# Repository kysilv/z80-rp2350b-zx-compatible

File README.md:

# z80-rp2350b-zx-compatible
This is a retrocomputer compatible with ZX Spectrum and based on real Z80 + discrete RAM/ROM + rp2350b to cover ULA functionality programmatically.

## Specification:

**CPU**: Z84C00AB6 Z80A CPU DIP-40

**ROM**: W27c512-45z DIP-28

**RAM**: 2xHM62256ALP-10 DIP-28

**ULA**: WeAct RP2350B Core board

**Video**: VGA (DE-15) and DVI over HDMI connector, 720x576p emulating Spectrum PAL resolution.

**Audio**: Speaker on board

**Cassette interface**: Jack 3.5mm for smartphone headset jack

**Keyboard**: Handmade

**Joystick**: 
  1. Retro DA-15 GamePort joystick interface connected to expansion connector, emulating Kempston port 1F.
  2. Sinclair Joystick 1 in parallel to keyboard 6-0 (connector not soldered yet).

## Folders:

**firmware**: Source code for rp2350b covering ULA functionality (C + PIO ASM)

**hardware**: Pictures of schematic and pcbs, KiCAD projects of the computer and Joystick interface. There are pictures of the first version with a lot of fixes. 

**photos**: Photos of the device in process of tuning and some "screenshots".

Press: https://hackaday.com/2026/07/13/its-a-spectrum-with-an-rp2350-ula/

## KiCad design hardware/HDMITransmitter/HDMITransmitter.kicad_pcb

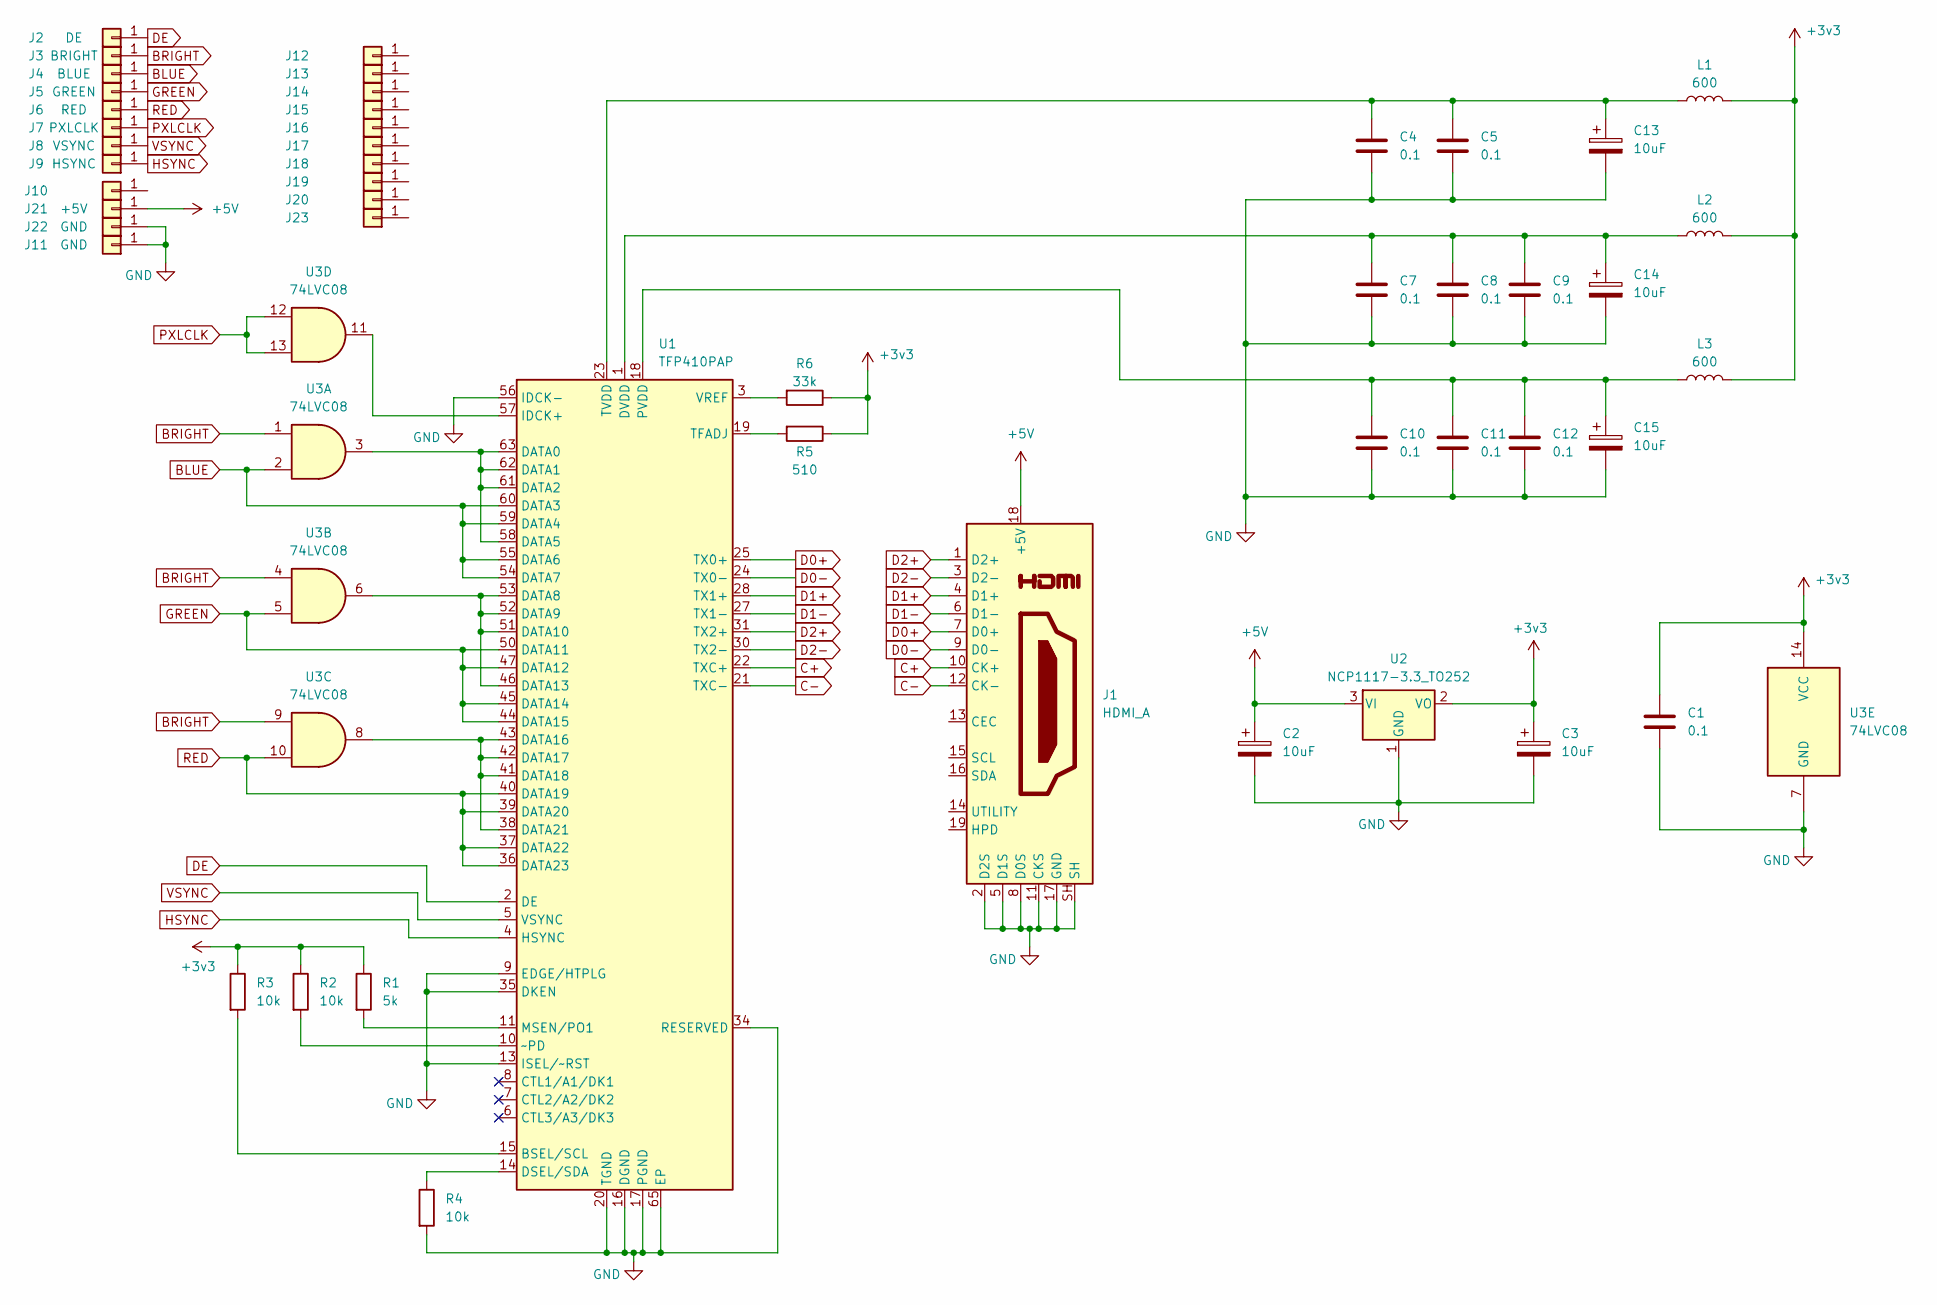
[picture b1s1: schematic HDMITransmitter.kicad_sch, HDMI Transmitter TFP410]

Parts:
C1, C4, C5, C7, C8, C9, C10, C11, C12: 0.1; C_0603_1608Metric_Pad1.08x0.95mm_HandSolder
C2, C3, C13, C14, C15: 10uF; CP_EIA-3216-18_Kemet-A_HandSolder
J1: HDMI_A; HDMI_A_Molex_208658-1001_Horizontal
J2: DE; Pin_D1.0mm_L10.0mm
J3: BRIGHT; Pin_D1.0mm_L10.0mm
J4: BLUE; Pin_D1.0mm_L10.0mm
J5: GREEN; Pin_D1.0mm_L10.0mm
J6: RED; Pin_D1.0mm_L10.0mm
J7: PXLCLK; Pin_D1.0mm_L10.0mm
J8: VSYNC; Pin_D1.0mm_L10.0mm
J9: HSYNC; Pin_D1.0mm_L10.0mm
J10, J12, J13, J14, J15, J16, J17, J18, J19, J20, J23: Pin_D1.0mm_L10.0mm
J11, J22: GND; Pin_D1.0mm_L10.0mm
J21: +5V; Pin_D1.0mm_L10.0mm
L1, L2, L3: 600; L_0603_1608Metric_Pad1.05x0.95mm_HandSolder
R1: 5k; R_0603_1608Metric_Pad0.98x0.95mm_HandSolder
R2, R3, R4: 10k; R_0603_1608Metric_Pad0.98x0.95mm_HandSolder
R5: 510; R_0603_1608Metric_Pad0.98x0.95mm_HandSolder
R6: 33k; R_0603_1608Metric_Pad0.98x0.95mm_HandSolder
U1: TFP410PAP; Texas_TQFP-64-1EP_10x10mm_P0.5mm_EP8x8mm_Mask5x5mm_ThermalV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
U2: NCP1117-3.3_TO252; TO-252-2
U3: 74LVC08; SOIC-14_3.9x8.7mm_P1.27mm

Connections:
+3v3: C1.1, C3.1, L1.2, L2.2, L3.2, R1.1, R2.1, R3.1, R5.1, R6.1, U2.2 (VO), U3.14 (VCC)
+5V: C2.1, J1.18 (+5V), J21.1, U2.3 (VI)
BLUE: J4.1, U1.54 (DATA7), U1.55 (DATA6), U1.59 (DATA4), U1.60 (DATA3), U3.2
BRIGHT: J3.1, U3.1, U3.4, U3.9
C+: J1.10 (CK+), U1.22 (TXC+)
C-: J1.12 (CK-), U1.21 (TXC-)
D0+: J1.7 (D0+), U1.25 (TX0+)
D0-: J1.9 (D0-), U1.24 (TX0-)
D1+: J1.4 (D1+), U1.28 (TX1+)
D1-: J1.6 (D1-), U1.27 (TX1-)
D2+: J1.1 (D2+), U1.31 (TX2+)
D2-: J1.3 (D2-), U1.30 (TX2-)
DE: J2.1, U1.2 (DE)
GND: C1.2, C2.2, C3.2, C4.2, C5.2, C7.2, C8.2, C9.2, C10.2, C11.2, C12.2, C13.2, C14.2, C15.2, J1.2 (D2S), J1.5 (D1S), J1.8 (D0S), J1.11 (CKS), J1.17 (GND), J1.SH, J11.1, J22.1, R4.2, U1.9 (EDGE/HTPLG), U1.13 (ISEL/~RST), U1.16 (DGND), U1.17 (PGND), U1.20 (TGND), U1.26 (TGND), U1.32 (TGND), U1.34 (RESERVED), U1.35 (DKEN), U1.48 (DGND), U1.56 (IDCK-), U1.64 (DGND), U1.65 (EP), U2.1 (GND), U3.7 (GND)
GREEN: J5.1, U1.44 (DATA15), U1.45 (DATA14), U1.47 (DATA12), U1.50 (DATA11), U3.5
HSYNC: J9.1, U1.4 (HSYNC)
unnamed: C4.1, C5.1, C13.1, L1.1, U1.23 (TVDD), U1.29 (TVDD)
unnamed: C7.1, C8.1, C9.1, C14.1, L2.1, U1.1 (DVDD), U1.12 (DVDD), U1.33 (DVDD)
unnamed: R3.2, U1.15 (BSEL/SCL)
unnamed: U1.58 (DATA5), U1.61 (DATA2), U1.62 (DATA1), U1.63 (DATA0), U3.3
unnamed: U1.46 (DATA13), U1.51 (DATA10), U1.52 (DATA9), U1.53 (DATA8), U3.6
unnamed: U1.38 (DATA21), U1.41 (DATA18), U1.42 (DATA17), U1.43 (DATA16), U3.8
unnamed: R4.1, U1.14 (DSEL/SDA)
unnamed: U1.57 (IDCK+), U3.11
unnamed: R1.2, U1.11 (MSEN/PO1)
unnamed: C10.1, C11.1, C12.1, C15.1, L3.1, U1.18 (PVDD)
unnamed: R5.2, U1.19 (TFADJ)
unnamed: R6.2, U1.3 (VREF)
unnamed: R2.2, U1.10 (~PD)
PXLCLK: J7.1, U3.12, U3.13
RED: J6.1, U1.36 (DATA23), U1.37 (DATA22), U1.39 (DATA20), U1.40 (DATA19), U3.10
VSYNC: J8.1, U1.5 (VSYNC)

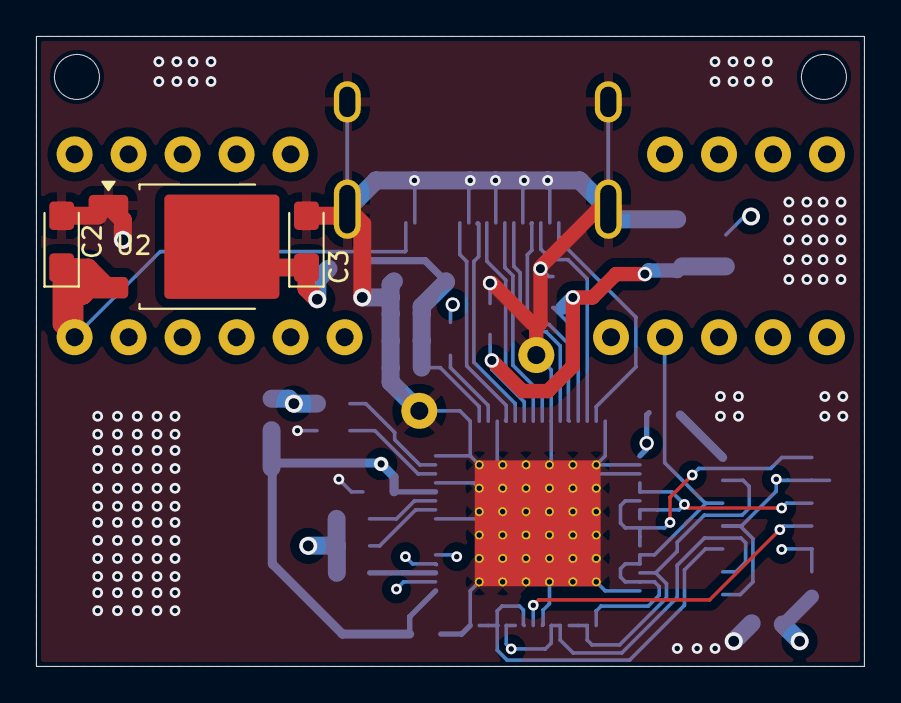
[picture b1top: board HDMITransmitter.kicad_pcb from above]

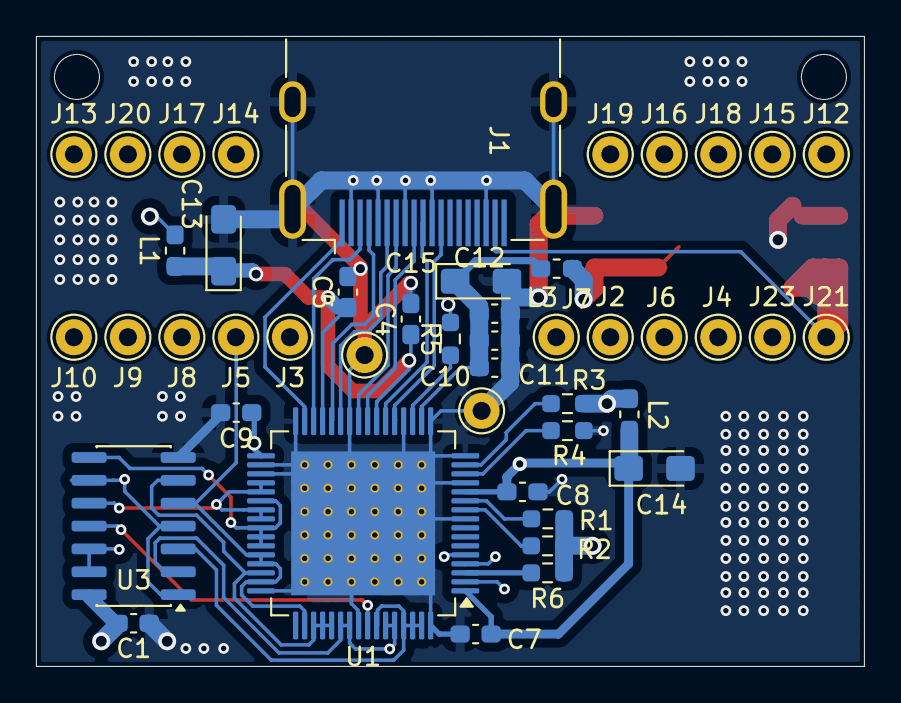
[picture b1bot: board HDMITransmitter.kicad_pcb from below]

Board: 4 copper layers, 46.0 x 35.0 mm, 49 parts (46 on the bottom side), 32 nets.

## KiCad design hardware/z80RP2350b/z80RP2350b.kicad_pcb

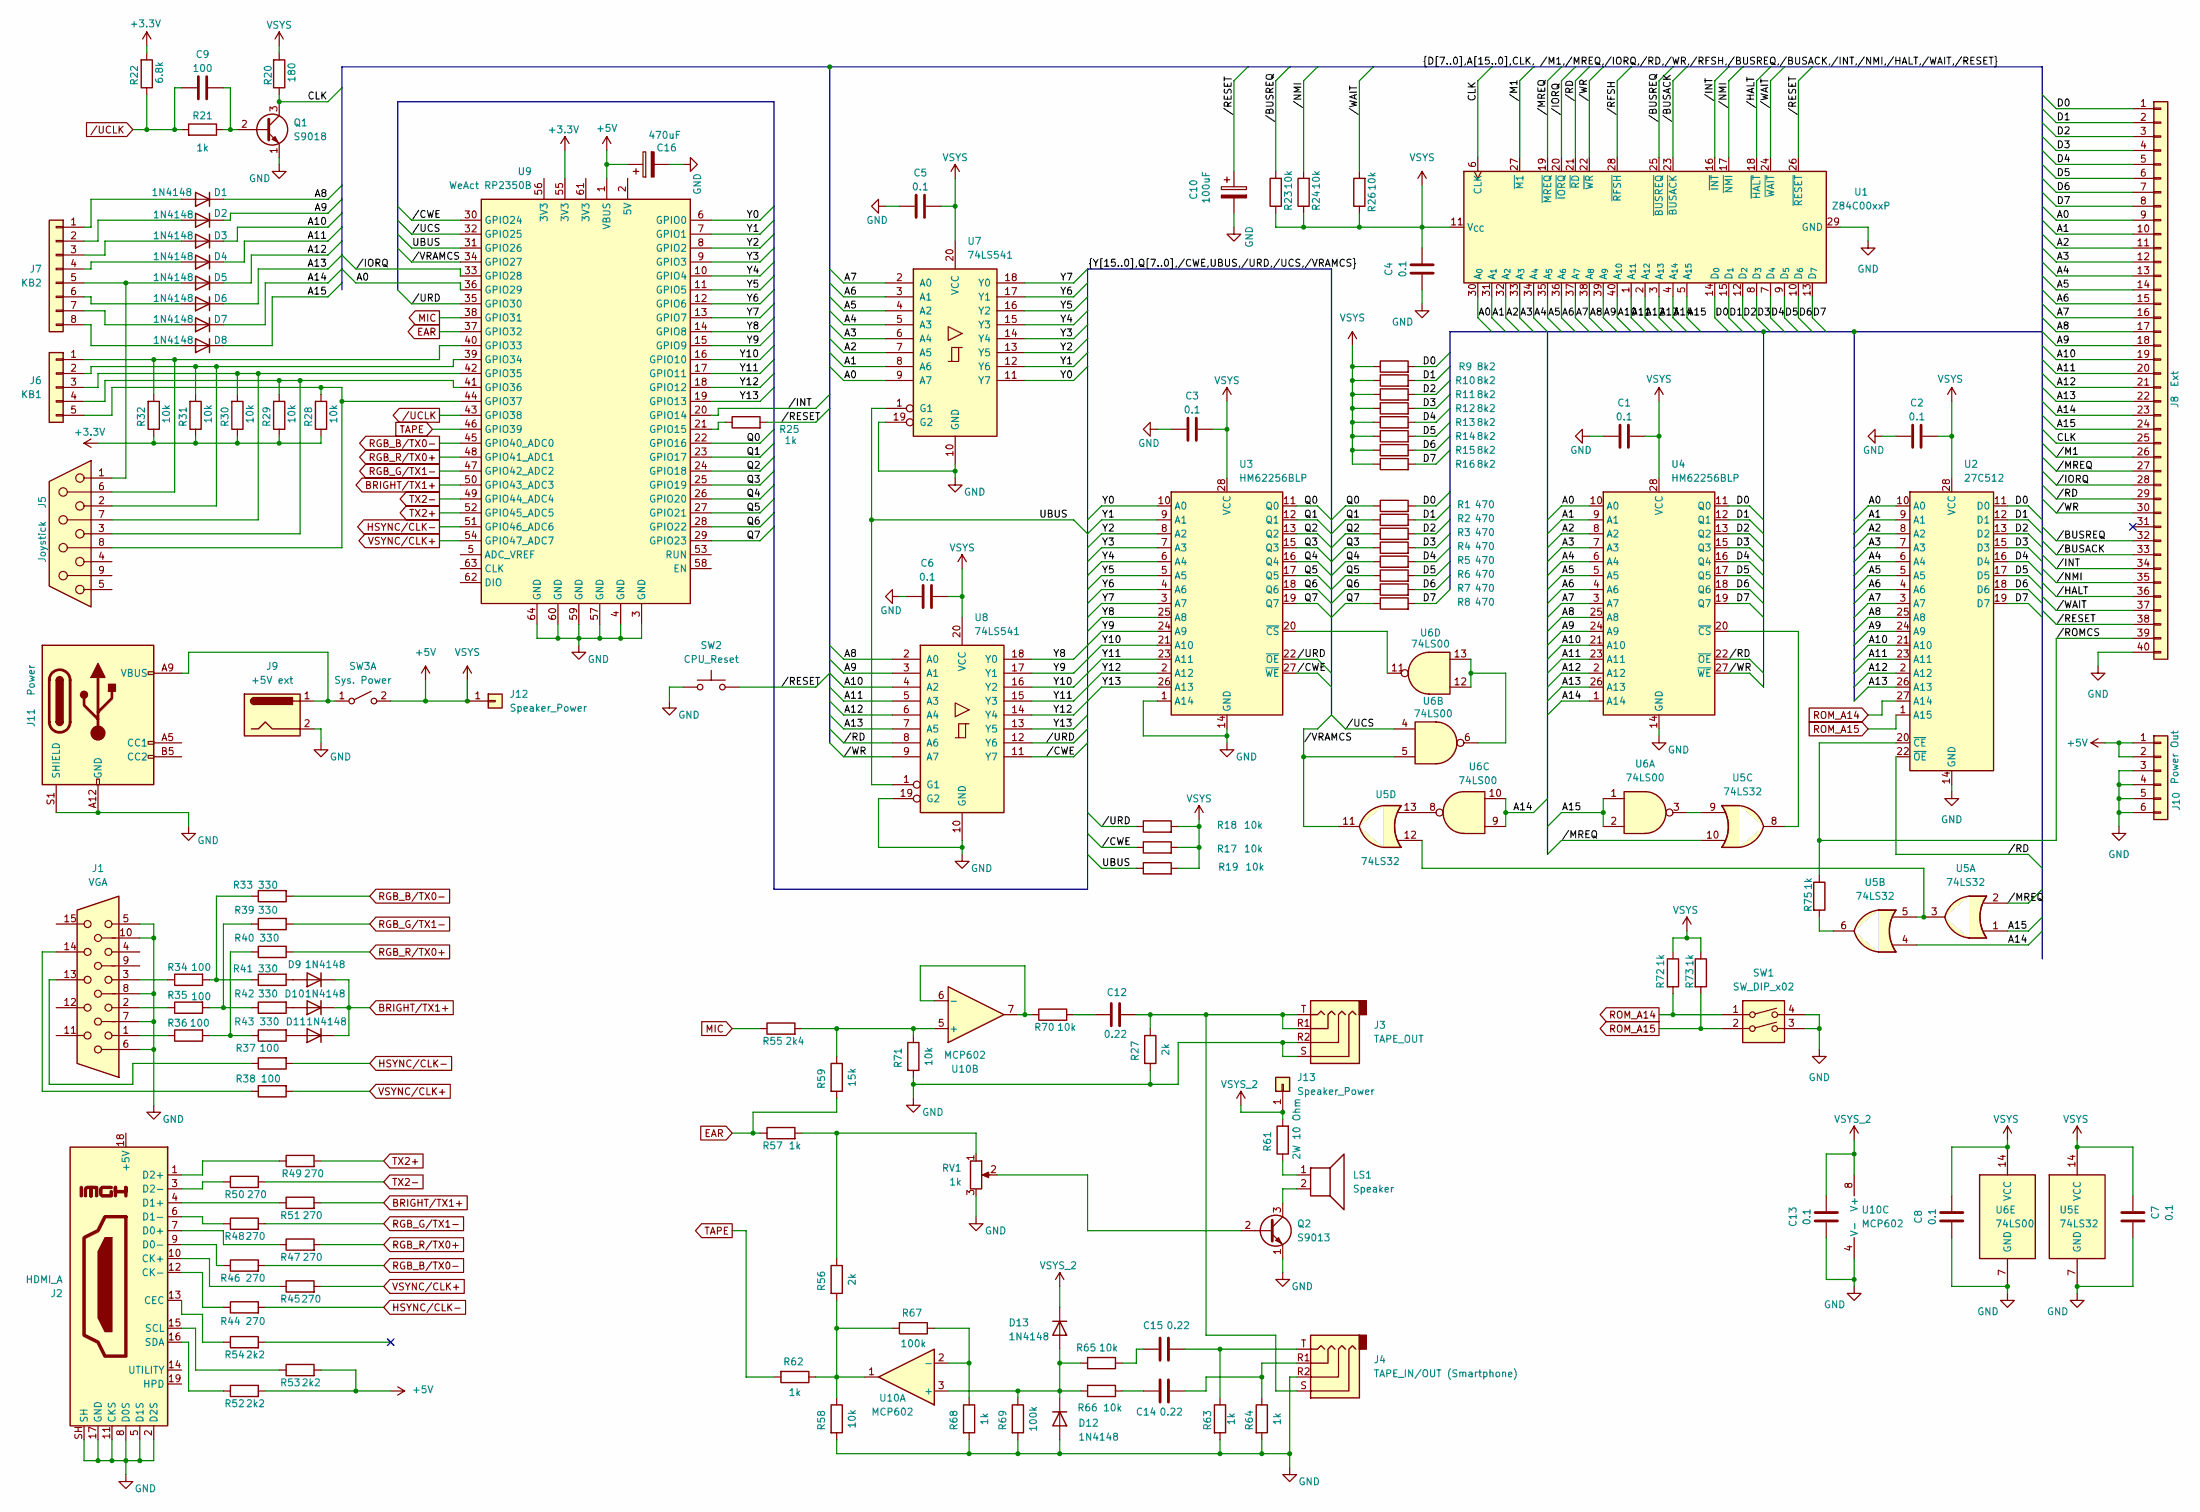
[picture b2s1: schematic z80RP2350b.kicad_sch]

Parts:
C1, C2, C3, C4, C5, C6, C7, C8, C13: 0.1; C_Disc_D7.5mm_W5.0mm_P7.50mm
C9: 100; C_Disc_D7.5mm_W5.0mm_P7.50mm
C10: 100uF; CP_Radial_D5.0mm_P2.00mm
C12, C14, C15: 0.22; C_Disc_D7.5mm_W5.0mm_P7.50mm
C16: 470uF; CP_Radial_D5.0mm_P2.00mm
D1, D2, D3, D4, D5, D6, D7, D8, D9, D10, D11, D12, D13: 1N4148; D_DO-35_SOD27_P7.62mm_Horizontal
J1: VGA; DSUB-15-HD_Socket_Horizontal_P2.29x2.54mm_EdgePinOffset8.35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
J2: HDMI_A; HDMI_A_Kycon_KDMIX-SL1-NS-WS-B15_VerticalRightAngle
J3: TAPE_OUT; Jack_3.5mm_PJ320D_Horizontal
J4: TAPE_IN/OUT (Smartphone); Jack_3.5mm_PJ320D_Horizontal
J5: Joystick; DSUB-9_Socket_Vertical_P2.77x2.84mm
J6: KB1; PinHeader_1x05_P2.54mm_Vertical
J7: KB2; PinHeader_1x08_P2.54mm_Vertical
J8: Ext; PinHeader_2x20_P2.54mm_Vertical
J9: +5V ext; BarrelJack_GCT_DCJ200-10-A_Horizontal
J10: Power Out; PinHeader_2x03_P2.54mm_Vertical
J11: Power; USB_C_Receptacle_GCT_USB4125-xx-x_6P_TopMnt_Horizontal
J12, J13: Speaker_Power; PinSocket_1x01_P2.54mm_Vertical
LS1: Speaker; PinHeader_1x02_P2.54mm_Vertical
Q1: S9018; TO-92
Q2: S9013; TO-92
R1, R2, R3, R4, R5, R6, R7, R8: 470; R_Axial_DIN0207_L6.3mm_D2.5mm_P10.16mm_Horizontal
R9, R10, R11, R12, R13, R14, R15, R16: 8k2; R_Axial_DIN0207_L6.3mm_D2.5mm_P10.16mm_Horizontal
R17, R18, R19, R23, R24, R26, R28, R29, R30, R31, R32, R58, R65, R66, R70, R71: 10k; R_Axial_DIN0207_L6.3mm_D2.5mm_P10.16mm_Horizontal
R20: 180; R_Axial_DIN0207_L6.3mm_D2.5mm_P10.16mm_Horizontal
R21, R25, R57, R62, R63, R64, R68, R72, R73, R75: 1k; R_Axial_DIN0207_L6.3mm_D2.5mm_P10.16mm_Horizontal
R22: 6.8k; R_Axial_DIN0207_L6.3mm_D2.5mm_P10.16mm_Horizontal
R27, R56: 2k; R_Axial_DIN0207_L6.3mm_D2.5mm_P10.16mm_Horizontal
R33, R39, R40, R41, R42, R43: 330; R_Axial_DIN0207_L6.3mm_D2.5mm_P10.16mm_Horizontal
R34, R35, R36, R37, R38: 100; R_Axial_DIN0207_L6.3mm_D2.5mm_P10.16mm_Horizontal
R44, R45, R46, R47, R48, R49, R50, R51: 270; R_Axial_DIN0207_L6.3mm_D2.5mm_P10.16mm_Horizontal
R52, R53, R54: 2k2; R_Axial_DIN0207_L6.3mm_D2.5mm_P10.16mm_Horizontal
R55: 2k4; R_Axial_DIN0207_L6.3mm_D2.5mm_P10.16mm_Horizontal
R59: 15k; R_Axial_DIN0207_L6.3mm_D2.5mm_P10.16mm_Horizontal
R61: 2W 10 Ohm; R_Axial_DIN0411_L9.9mm_D3.6mm_P7.62mm_Vertical
R67, R69: 100k; R_Axial_DIN0207_L6.3mm_D2.5mm_P10.16mm_Horizontal
RV1: 1k; Potentiometer_ACP_CA9-V10_Vertical_Hole
SW1: SW_DIP_x02; SW_DIP_SPSTx02_Slide_9.78x7.26mm_W7.62mm_P2.54mm
SW2: CPU_Reset; PinHeader_1x02_P2.54mm_Vertical
SW3: Sys. Power; PinHeader_1x02_P2.54mm_Vertical
U1: Z84C00xxP; DIP-40_W15.24mm
U2: 27C512; DIP-28_W15.24mm
U3, U4: HM62256BLP; DIP-28_W15.24mm
U5: 74LS32; DIP-14_W7.62mm
U6: 74LS00; DIP-14_W7.62mm
U7, U8: 74LS541; DIP-20_W7.62mm
U9: WeAct RP2350B; WeAct_RP2350b
U10: MCP602; DIP-8_W7.62mm

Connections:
+3.3V: R22.2, R28.1, R29.1, R30.1, R31.1, R32.1, U9.55 (3V3)
+5V: C1.1, C2.1, C3.1, C4.1, C5.1, C6.1, C7.1, C8.1, C16.1, J10.1, J10.2, J12.1, R9.1, R10.1, R11.1, R12.1, R13.1, R14.1, R15.1, R16.1, R17.2, R18.2, R19.2, R20.2, R23.1, R24.1, R26.1, R52.2, R53.2, R72.1, R73.1, SW3.2 (B), U1.11 (V_{CC}), U2.28 (VCC), U3.28 (VCC), U4.28 (VCC), U5.14 (VCC), U6.14 (VCC), U7.20 (VCC), U8.20 (VCC), U9.1 (VBUS)
/A0: J8.9, U1.30 (A_{0}), U2.10 (A0), U4.10 (A0), U7.9 (A7), U9.36 (GPIO29)
/A1: J8.10, U1.31 (A_{1}), U2.9 (A1), U4.9 (A1), U7.8 (A6)
/A2: J8.11, U1.32 (A_{2}), U2.8 (A2), U4.8 (A2), U7.7 (A5)
/A3: J8.12, U1.33 (A_{3}), U2.7 (A3), U4.7 (A3), U7.6 (A4)
/A4: J8.13, U1.34 (A_{4}), U2.6 (A4), U4.6 (A4), U7.5 (A3)
/A5: J8.14, U1.35 (A_{5}), U2.5 (A5), U4.5 (A5), U7.4 (A2)
/A6: J8.15, U1.36 (A_{6}), U2.4 (A6), U4.4 (A6), U7.3 (A1)
/A7: J8.16, U1.37 (A_{7}), U2.3 (A7), U4.3 (A7), U7.2 (A0)
/A8: D1.1 (K), J8.17, U1.38 (A_{8}), U2.25 (A8), U4.25 (A8), U8.2 (A0)
/A9: D2.1 (K), J8.18, U1.39 (A_{9}), U2.24 (A9), U4.24 (A9), U8.3 (A1)
/A10: D3.1 (K), J8.19, U1.40 (A_{10}), U2.21 (A10), U4.21 (A10), U8.4 (A2)
/A11: D4.1 (K), J8.20, U1.1 (A_{11}), U2.23 (A11), U4.23 (A11), U8.5 (A3)
/A12: D5.1 (K), J8.21, U1.2 (A_{12}), U2.2 (A12), U4.2 (A12), U8.6 (A4)
/A13: D6.1 (K), J8.22, U1.3 (A_{13}), U2.26 (A13), U4.26 (A13), U8.7 (A5)
/A14: D7.1 (K), J8.23, U1.4 (A_{14}), U4.1 (A14), U5.4, U6.9, U6.10
/A15: D8.1 (K), J8.24, U1.5 (A_{15}), U5.1, U6.1, U6.2
/CLK: J8.25, Q1.3 (C), R20.1, U1.6 (CLK)
/D0: J8.1, R1.2, R9.2, U1.14 (D_{0}), U2.11 (D0), U4.11 (Q0)
/D1: J8.2, R2.2, R10.2, U1.15 (D_{1}), U2.12 (D1), U4.12 (Q1)
/D2: J8.3, R3.2, R11.2, U1.12 (D_{2}), U2.13 (D2), U4.13 (Q2)
/D3: J8.4, R4.2, R12.2, U1.8 (D_{3}), U2.15 (D3), U4.15 (Q3)
/D4: J8.5, R5.2, R13.2, U1.7 (D_{4}), U2.16 (D4), U4.16 (Q4)
/D5: J8.6, R6.2, R14.2, U1.9 (D_{5}), U2.17 (D5), U4.17 (Q5)
/D6: J8.7, R7.2, R15.2, U1.10 (D_{6}), U2.18 (D6), U4.18 (Q6)
/D7: J8.8, R8.2, R16.2, U1.13 (D_{7}), U2.19 (D7), U4.19 (Q7)
/Q0: R1.1, U3.11 (Q0), U9.22 (GPIO16)
/Q1: R2.1, U3.12 (Q1), U9.23 (GPIO17)
/Q2: R3.1, U3.13 (Q2), U9.24 (GPIO18)
/Q3: R4.1, U3.15 (Q3), U9.25 (GPIO19)
/Q4: R5.1, U3.16 (Q4), U9.26 (GPIO20)
/Q5: R6.1, U3.17 (Q5), U9.27 (GPIO21)
/Q6: R7.1, U3.18 (Q6), U9.28 (GPIO22)
/Q7: R8.1, U3.19 (Q7), U9.29 (GPIO23)
/UBUS: R19.1, U7.1 (G1), U8.1 (G1), U9.31 (GPIO26)
/Y0: U3.10 (A0), U7.11 (Y7), U9.6 (GPIO0)
/Y1: U3.9 (A1), U7.12 (Y6), U9.7 (GPIO1)
/Y2: U3.8 (A2), U7.13 (Y5), U9.8 (GPIO2)
/Y3: U3.7 (A3), U7.14 (Y4), U9.9 (GPIO3)
/Y4: U3.6 (A4), U7.15 (Y3), U9.10 (GPIO4)
/Y5: U3.5 (A5), U7.16 (Y2), U9.11 (GPIO5)
/Y6: U3.4 (A6), U7.17 (Y1), U9.12 (GPIO6)
/Y7: U3.3 (A7), U7.18 (Y0), U9.13 (GPIO7)
/Y8: U3.25 (A8), U8.18 (Y0), U9.14 (GPIO8)
/Y9: U3.24 (A9), U8.17 (Y1), U9.15 (GPIO9)
/Y10: U3.21 (A10), U8.16 (Y2), U9.16 (GPIO10)
/Y11: U3.23 (A11), U8.15 (Y3), U9.17 (GPIO11)
/Y12: U3.2 (A12), U8.14 (Y4), U9.18 (GPIO12)
/Y13: U3.26 (A13), U8.13 (Y5), U9.19 (GPIO13)
//BUSACK: J8.33, U1.23 (~BUSACK)
//BUSREQ: J8.32, R23.2, U1.25 (~BUSREQ)
//CWE: R17.1, U3.27 (~WE), U8.11 (Y7), U9.30 (GPIO24)
//HALT: J8.36, U1.18 (~HALT)
//INT: J8.34, U1.16 (~INT), U9.20 (GPIO14)
//IORQ: J8.28, U1.20 (~IORQ), U9.33 (GPIO28)
//M1: J8.26, U1.27 (~M1)
//MREQ: J8.27, U1.19 (~MREQ), U5.2, U5.10
//NMI: J8.35, R24.2, U1.17 (~NMI)
//RD: J8.29, U1.21 (~RD), U2.22 (~OE), U4.22 (~OE), U8.8 (A6)
//RESET: C10.1, J8.38, R25.2, SW2.2, U1.26 (~RESET)
//RFSH: U1.28 (~RFSH)
//ROMCS: J8.39, R75.1, U2.20 (~CE)
//UCS: U6.4, U9.32 (GPIO25)
//URD: R18.1, U3.22 (~OE), U8.12 (Y6), U9.35 (GPIO30)
//VRAMCS: U5.11, U6.5, U9.34 (GPIO27)
//WAIT: J8.37, R26.2, U1.24 (~WAIT)
//WR: J8.30, U1.22 (~WR), U4.27 (~WE), U8.9 (A7)
BRIGHT/TX1+: D9.1 (K), D10.1 (K), D11.1 (K), R51.2, U9.50 (GPIO43_ADC3)
EAR: R57.1, R59.2, U9.37 (GPIO32)
GND: C1.2, C2.2, C3.2, C4.2, C5.2, C6.2, C7.2, C8.2, C10.2, C13.2, C16.2, D12.2 (A), J1.5, J1.6, J1.7, J1.8, J1.10, J2.2 (D2S), J2.5 (D1S), J2.8 (D0S), J2.11 (CKS), J2.17 (GND), J2.SH, J3.R2, J3.S, J4.R2, J8.40, J9.2, J10.3, J10.4, J10.5, J10.6, J11.A12 (GND), J11.B12 (GND), J11.S1 (SHIELD), Q1.1 (E), Q2.1 (E), R27.2, R58.2, R63.2, R64.2, R68.2, R69.2, R71.2, RV1.3, SW1.3, SW1.4, SW2.1, U1.29 (GND), U2.14 (GND), U3.1 (A14), U3.14 (GND), U4.14 (GND), U5.7 (GND), U6.7 (GND), U7.10 (GND), U7.19 (G2), U8.10 (GND), U8.19 (G2), U9.3 (GND), U9.4 (GND), U9.57 (GND), U9.59 (GND), U9.60 (GND), U9.64 (GND), U10.4 (V-)
HSYNC/CLK-: R37.2, R44.2, U9.51 (GPIO46_ADC6)
MIC: R55.1, U9.38 (GPIO31)
unnamed: C12.1, R70.2
unnamed: C12.2, J3.R1, J3.T, J4.S, R27.1
unnamed: C14.1, R66.1
unnamed: C14.2, J4.R1, R64.1
unnamed: C15.1, R65.1
unnamed: C15.2, J4.T, R63.1
unnamed: D1.2 (A), J7.1
unnamed: D2.2 (A), J7.2
unnamed: D3.2 (A), J7.3
unnamed: D4.2 (A), J7.4
unnamed: D5.2 (A), J5.1, J7.5
unnamed: D6.2 (A), J7.6
unnamed: D7.2 (A), J7.7
unnamed: D8.2 (A), J7.8
unnamed: D9.2 (A), R41.2
unnamed: D10.2 (A), R42.2
unnamed: D11.2 (A), R43.2
unnamed: D12.1 (K), D13.2 (A), R65.2, R66.2, R69.1, U10.3 (+)
unnamed: J1.1, R36.1
unnamed: J1.2, R35.1
unnamed: J1.3, R34.1
unnamed: J1.13, R37.1
unnamed: J1.14, R38.1
unnamed: J2.13 (CEC), R54.1
unnamed: J2.10 (CK+), R45.1
unnamed: J2.12 (CK-), R44.1
unnamed: J2.7 (D0+), R47.1
unnamed: J2.9 (D0-), R46.1
unnamed: J2.4 (D1+), R51.1
unnamed: J2.6 (D1-), R48.1
unnamed: J2.1 (D2+), R49.1
unnamed: J2.3 (D2-), R50.1
unnamed: J2.15 (SCL), R53.1
unnamed: J2.16 (SDA), R52.1
unnamed: J5.6, J6.1, R32.2, U9.40 (GPIO33)
unnamed: J5.2, J6.2, R31.2, U9.39 (GPIO34)
unnamed: J5.7, J6.3, R30.2, U9.42 (GPIO35)
unnamed: J5.3, J6.4, R29.2, U9.41 (GPIO36)
unnamed: J5.8, J6.5, R28.2, U9.44 (GPIO37)
unnamed: LS1.1, R61.1
unnamed: C9.2, Q1.2 (B), R21.1
unnamed: Q2.2 (B), RV1.2
unnamed: LS1.2, Q2.3 (C)
unnamed: R33.1, R34.2, R41.1
unnamed: R35.2, R39.1, R42.1
unnamed: R36.2, R40.1, R43.1
unnamed: R56.1, R57.2, RV1.1
unnamed: R56.2, R58.1, R62.1, R67.2, U10.1
unnamed: R75.2, U5.6
unnamed: J9.1, J11.A9 (VBUS), J11.B9 (VBUS), SW3.1 (A)
unnamed: U3.20 (~CS), U6.11
unnamed: U4.20 (~CS), U5.8
unnamed: U5.9, U6.3
unnamed: U5.3, U5.5, U5.12
unnamed: U5.13, U6.8
unnamed: U6.6, U6.12, U6.13
unnamed: R25.1, U9.21 (GPIO15)
unnamed: R67.1, R68.1, U10.2 (-)
unnamed: R55.2, R59.1, R71.1, U10.5 (+)
unnamed: R70.1, U10.6 (-), U10.7
RGB_B/TX0-: R33.2, R46.2, U9.45 (GPIO40_ADC0)
RGB_G/TX1-: R39.2, R48.2, U9.47 (GPIO42_ADC2)
RGB_R/TX0+: R40.2, R47.2, U9.48 (GPIO41_ADC1)
ROM_A14: R72.2, SW1.1, U2.27 (A14)
ROM_A15: R73.2, SW1.2, U2.1 (A15)
TAPE: R62.2, U9.46 (GPIO39)
TX2+: R49.2, U9.52 (GPIO45_ADC5)
TX2-: R50.2, U9.49 (GPIO44_ADC4)
VSYNC/CLK+: R38.2, R45.2, U9.54 (GPIO47_ADC7)
VSYS_2: C13.1, D13.1 (K), J13.1, R61.2, U10.8 (V+)
/UCLK: C9.1, R21.2, R22.1, U9.43 (GPIO38)

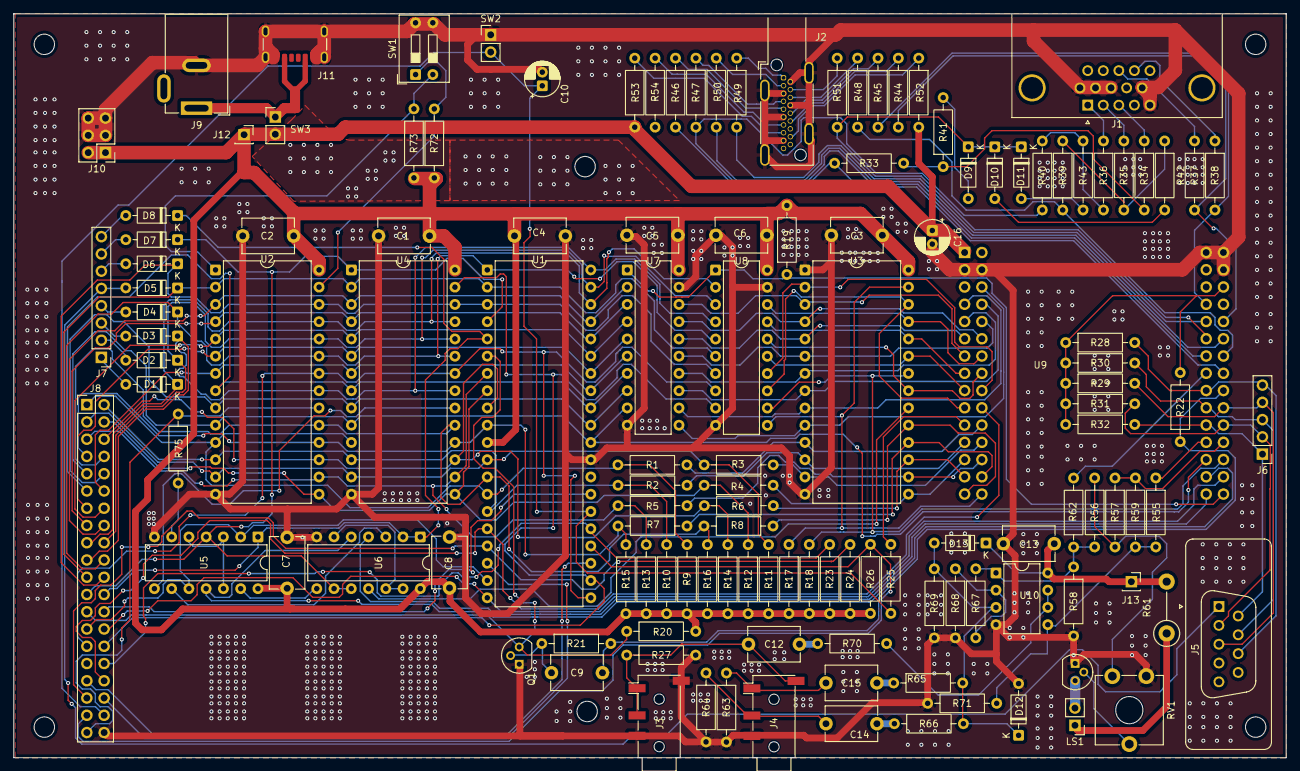
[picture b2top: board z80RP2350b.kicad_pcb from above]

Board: 2 copper layers, 187.3 x 109.5 mm, 131 parts (0 on the bottom side), 143 nets.

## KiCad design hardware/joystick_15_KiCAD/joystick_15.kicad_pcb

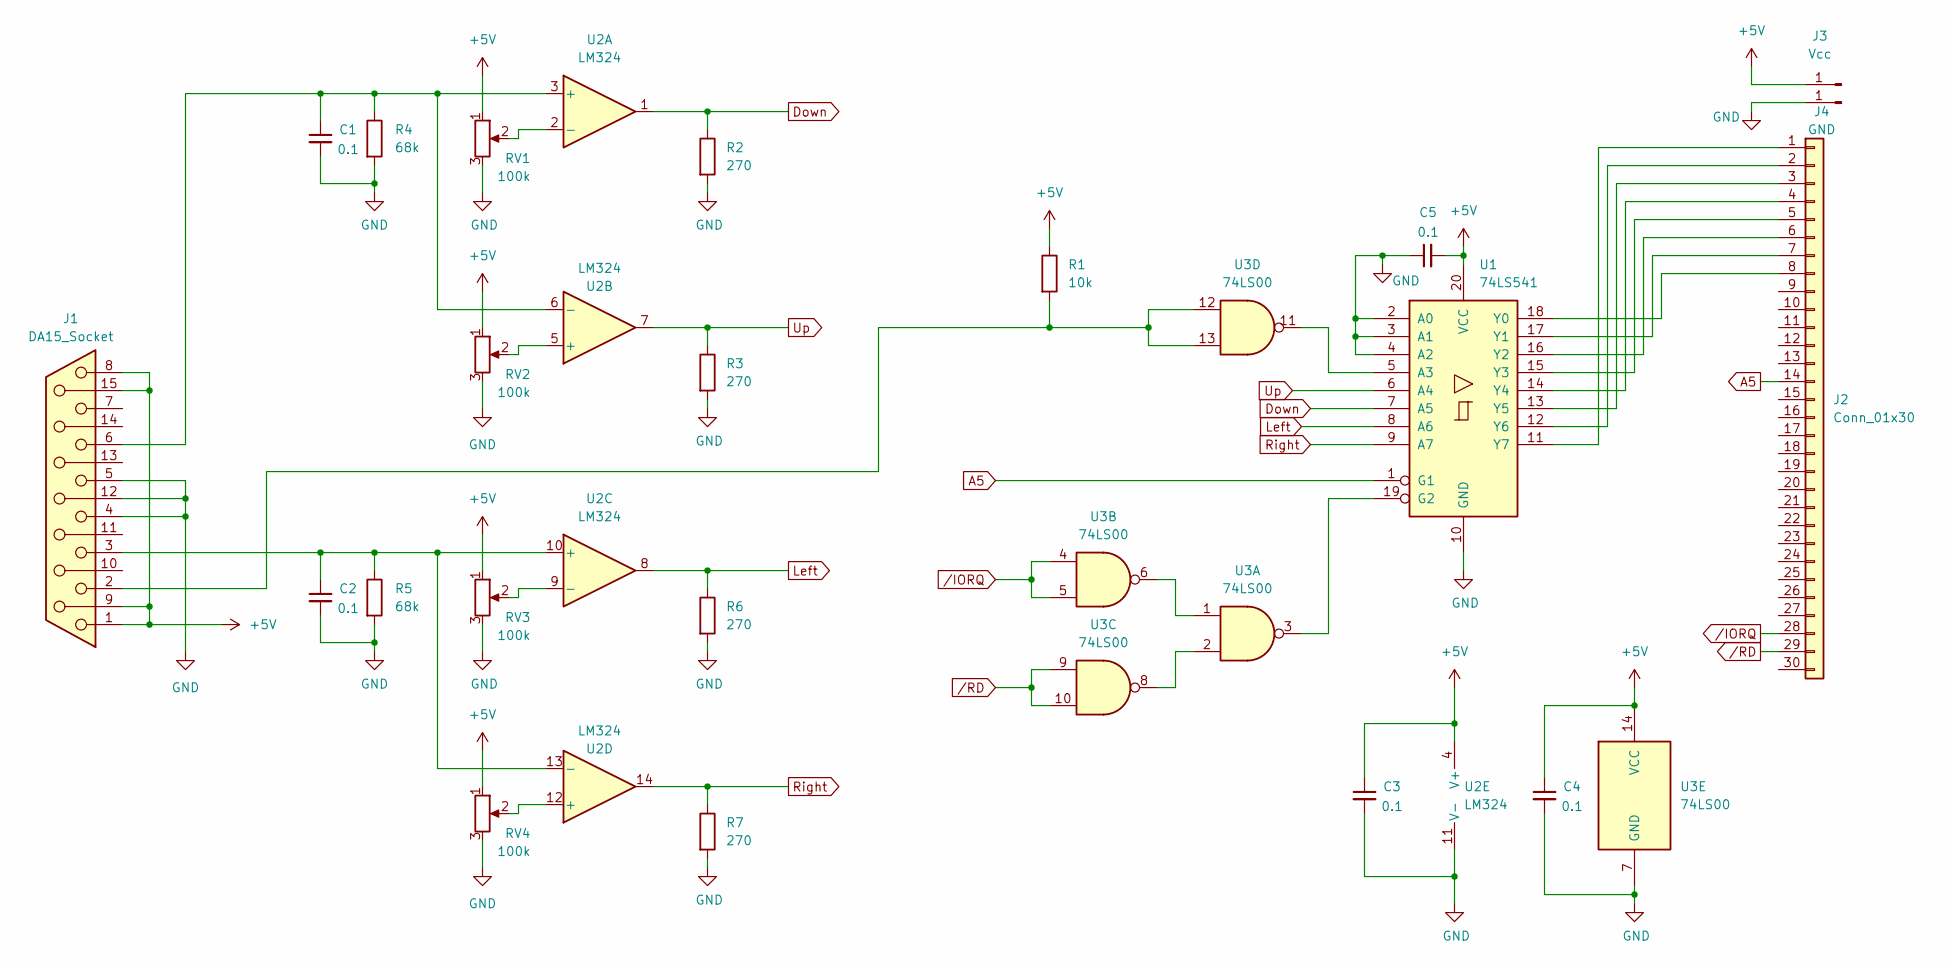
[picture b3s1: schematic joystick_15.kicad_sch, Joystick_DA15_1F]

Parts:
C1, C2, C3, C4, C5: 0.1; C_Disc_D4.7mm_W2.5mm_P5.00mm
J1: DA15_Socket; DSUB-15_Socket_Horizontal_P2.77x2.84mm_EdgePinOffset7.70mm_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
J2: Conn_01x30; PinSocket_2x15_P2.54mm_Vertical
J3: Vcc; Pin_D1.0mm_L10.0mm
J4: GND; Pin_D1.0mm_L10.0mm
R1: 10k; R_Axial_DIN0207_L6.3mm_D2.5mm_P7.62mm_Horizontal
R2, R3, R6, R7: 270; R_Axial_DIN0207_L6.3mm_D2.5mm_P7.62mm_Horizontal
R4, R5: 68k; R_Axial_DIN0207_L6.3mm_D2.5mm_P7.62mm_Horizontal
RV1, RV2, RV3, RV4: 100k; Potentiometer_Bourns_3296W_Vertical
U1: 74LS541; DIP-20_W7.62mm
U2: LM324; DIP-14_W7.62mm
U3: 74LS00; DIP-14_W7.62mm

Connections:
+5V: C3.1, C4.1, C5.2, J1.1, J1.8, J1.9, J1.15, J3.1, R1.1, RV1.1, RV2.1, RV3.1, RV4.1, U1.20 (VCC), U2.4 (V+), U3.14 (VCC)
A5: J2.14, U1.1 (G1)
Down: R2.1, U1.7 (A5), U2.1
GND: C1.2, C2.2, C3.2, C4.2, C5.1, J1.4, J1.5, J1.12, J4.1, R2.2, R3.2, R4.2, R5.2, R6.2, R7.2, RV1.3, RV2.3, RV3.3, RV4.3, U1.2 (A0), U1.3 (A1), U1.4 (A2), U1.10 (GND), U2.11 (V-), U3.7 (GND)
Left: R6.1, U1.8 (A6), U2.8
unnamed: J1.2, R1.2, U3.12, U3.13
unnamed: J2.1, U1.11 (Y7)
unnamed: J2.2, U1.12 (Y6)
unnamed: J2.3, U1.13 (Y5)
unnamed: J2.4, U1.14 (Y4)
unnamed: J2.5, U1.15 (Y3)
unnamed: J2.6, U1.16 (Y2)
unnamed: J2.7, U1.17 (Y1)
unnamed: J2.8, U1.18 (Y0)
unnamed: U1.5 (A3), U3.11
unnamed: U1.19 (G2), U3.3
unnamed: C1.1, J1.6, R4.1, U2.3 (+), U2.6 (-)
unnamed: RV1.2, U2.2 (-)
unnamed: RV2.2, U2.5 (+)
unnamed: C2.1, J1.3, R5.1, U2.10 (+), U2.13 (-)
unnamed: RV3.2, U2.9 (-)
unnamed: RV4.2, U2.12 (+)
unnamed: U3.1, U3.6
unnamed: U3.2, U3.8
Right: R7.1, U1.9 (A7), U2.14
Up: R3.1, U1.6 (A4), U2.7
/IORQ: J2.28, U3.4, U3.5
/RD: J2.29, U3.9, U3.10

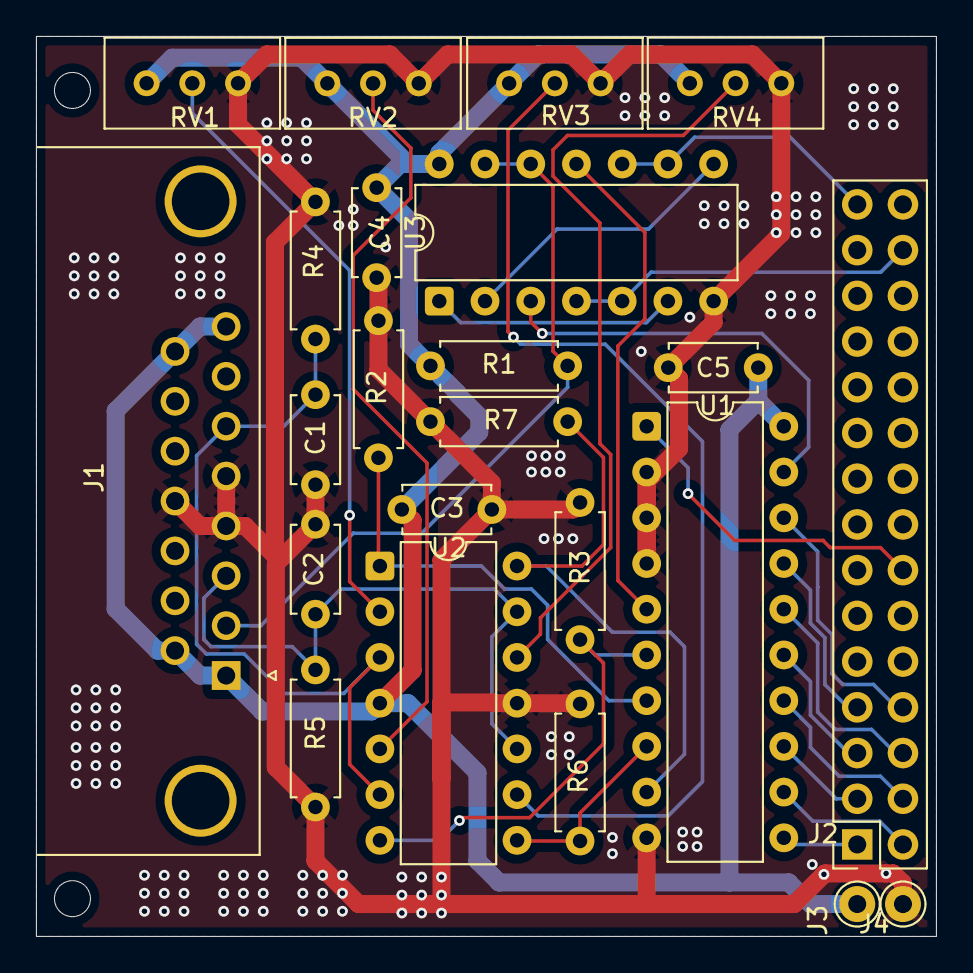
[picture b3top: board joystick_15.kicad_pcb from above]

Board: 2 copper layers, 50.0 x 50.0 mm, 23 parts (0 on the bottom side), 28 nets.

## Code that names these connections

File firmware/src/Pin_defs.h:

#define Y0 0
#define INT 14
#define Z80Reset 15

#define Q0 16
#define Q1 17
#define Q2 18
#define Q3 19
#define Q4 20
#define Q5 21
#define Q6 22
#define Q7 23

#define CWE 24
#define UCS 25
#define UBUS 26
#define VRAMCS 27
#define IORQ 28
#define A0 29
#define URD 30
#define MIC 31
#define EAR 32
#define KB1 33
#define KB2 34
#define KB3 35
#define KB4 36
#define KB5 37
#define UCLK 38
#define TAPE 39

#define VGA_B 40
#define VGA_R 41
#define VGA_G 42
#define BRIGHT 43
#define DE 44
#define PXLCLK 45
#define HSYNC 46
#define VSYNC 47

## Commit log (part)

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2026-06-24 Added photos and images
2026-06-24 Housekeeping - comments etc..
2026-06-24 Filename fixed
2026-06-24 Renamed files for better visibility
2026-06-29 added more photos
2026-06-30 KiCAD project for Joystock interface added
